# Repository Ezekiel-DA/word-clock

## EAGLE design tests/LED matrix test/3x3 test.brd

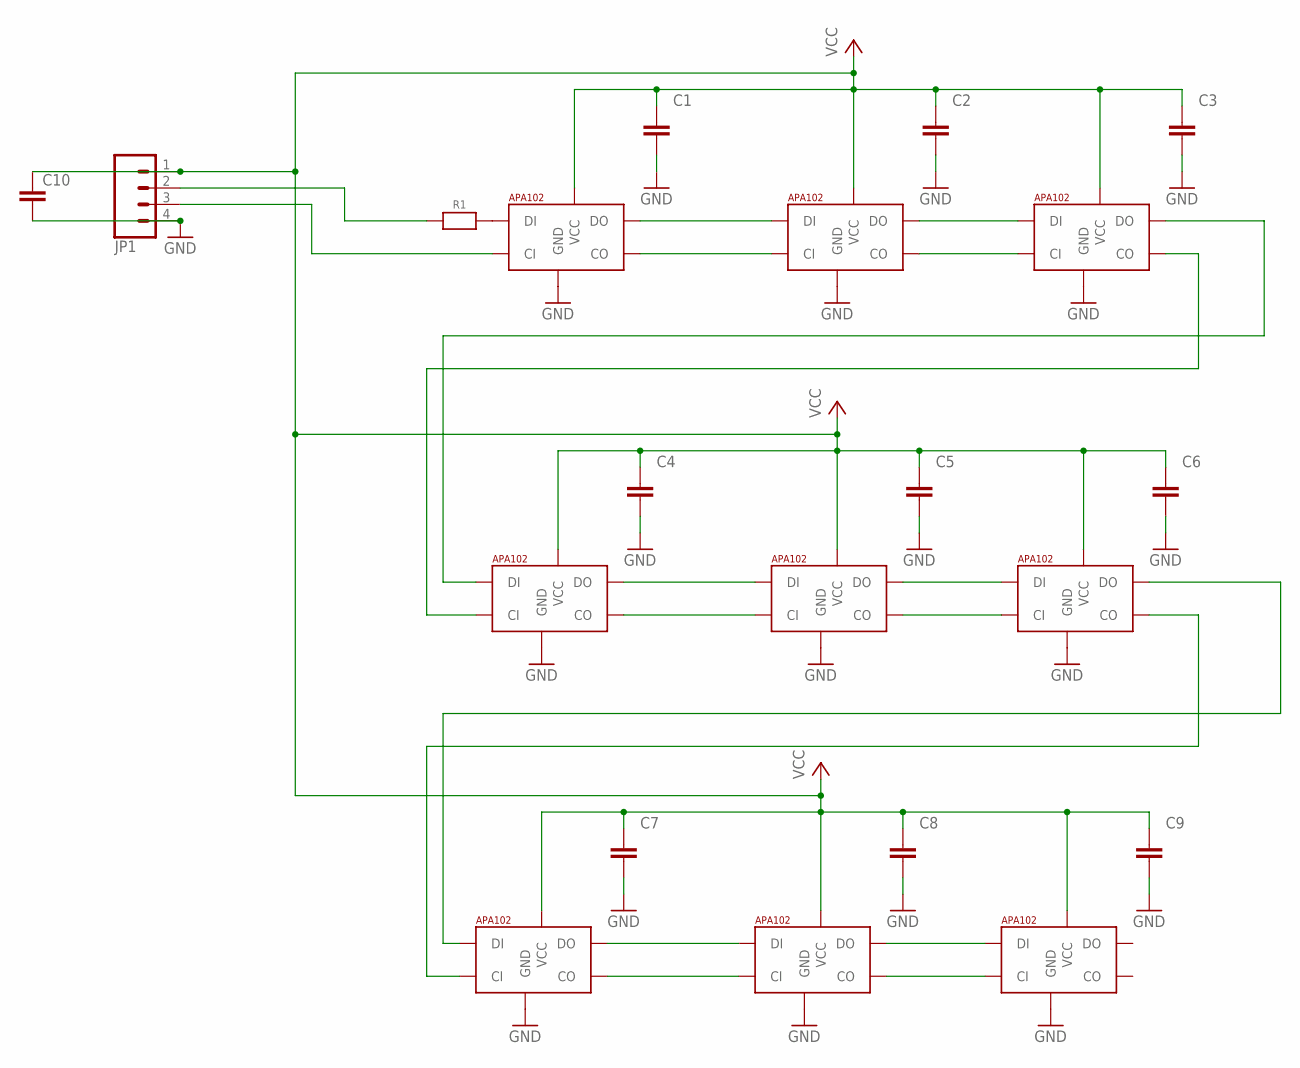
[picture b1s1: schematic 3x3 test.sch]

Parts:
C1, C2, C3, C4, C5, C6, C7, C8, C9: CAPACITOR_NPOL-0805; C805
C10: C-EUC0805; C0805
JP1: CONN_04; 1X04
R1: RESISTOR0805_NOOUTLINE; 0805-NO
U$1, U$2, U$3, U$4, U$5, U$6, U$7, U$8, U$9: APA1025050; APA102_5050

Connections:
GND: C1.2, C2.2, C3.2, C4.2, C5.2, C6.2, C7.2, C8.2, C9.2, C10.2, JP1.4, U$1.6 (GND), U$2.6 (GND), U$3.6 (GND), U$4.6 (GND), U$5.6 (GND), U$6.6 (GND), U$7.6 (GND), U$8.6 (GND), U$9.6 (GND)
unnamed: U$1.3 (DO), U$2.4 (DI)
unnamed: U$2.3 (DO), U$3.4 (DI)
unnamed: U$4.3 (DO), U$5.4 (DI)
unnamed: U$5.3 (DO), U$6.4 (DI)
unnamed: U$4.2 (CO), U$5.5 (CI)
unnamed: U$5.2 (CO), U$6.5 (CI)
unnamed: U$7.3 (DO), U$8.4 (DI)
unnamed: U$8.3 (DO), U$9.4 (DI)
unnamed: U$1.2 (CO), U$2.5 (CI)
unnamed: U$2.2 (CO), U$3.5 (CI)
unnamed: U$7.2 (CO), U$8.5 (CI)
unnamed: U$8.2 (CO), U$9.5 (CI)
unnamed: U$3.3 (DO), U$4.4 (DI)
unnamed: U$3.2 (CO), U$4.5 (CI)
unnamed: U$6.3 (DO), U$7.4 (DI)
unnamed: U$6.2 (CO), U$7.5 (CI)
unnamed: JP1.2, R1.1
unnamed: R1.2, U$1.4 (DI)
unnamed: JP1.3, U$1.5 (CI)
VCC: C1.1, C2.1, C3.1, C4.1, C5.1, C6.1, C7.1, C8.1, C9.1, C10.1, JP1.1, U$1.1 (VCC), U$2.1 (VCC), U$3.1 (VCC), U$4.1 (VCC), U$5.1 (VCC), U$6.1 (VCC), U$7.1 (VCC), U$8.1 (VCC), U$9.1 (VCC)

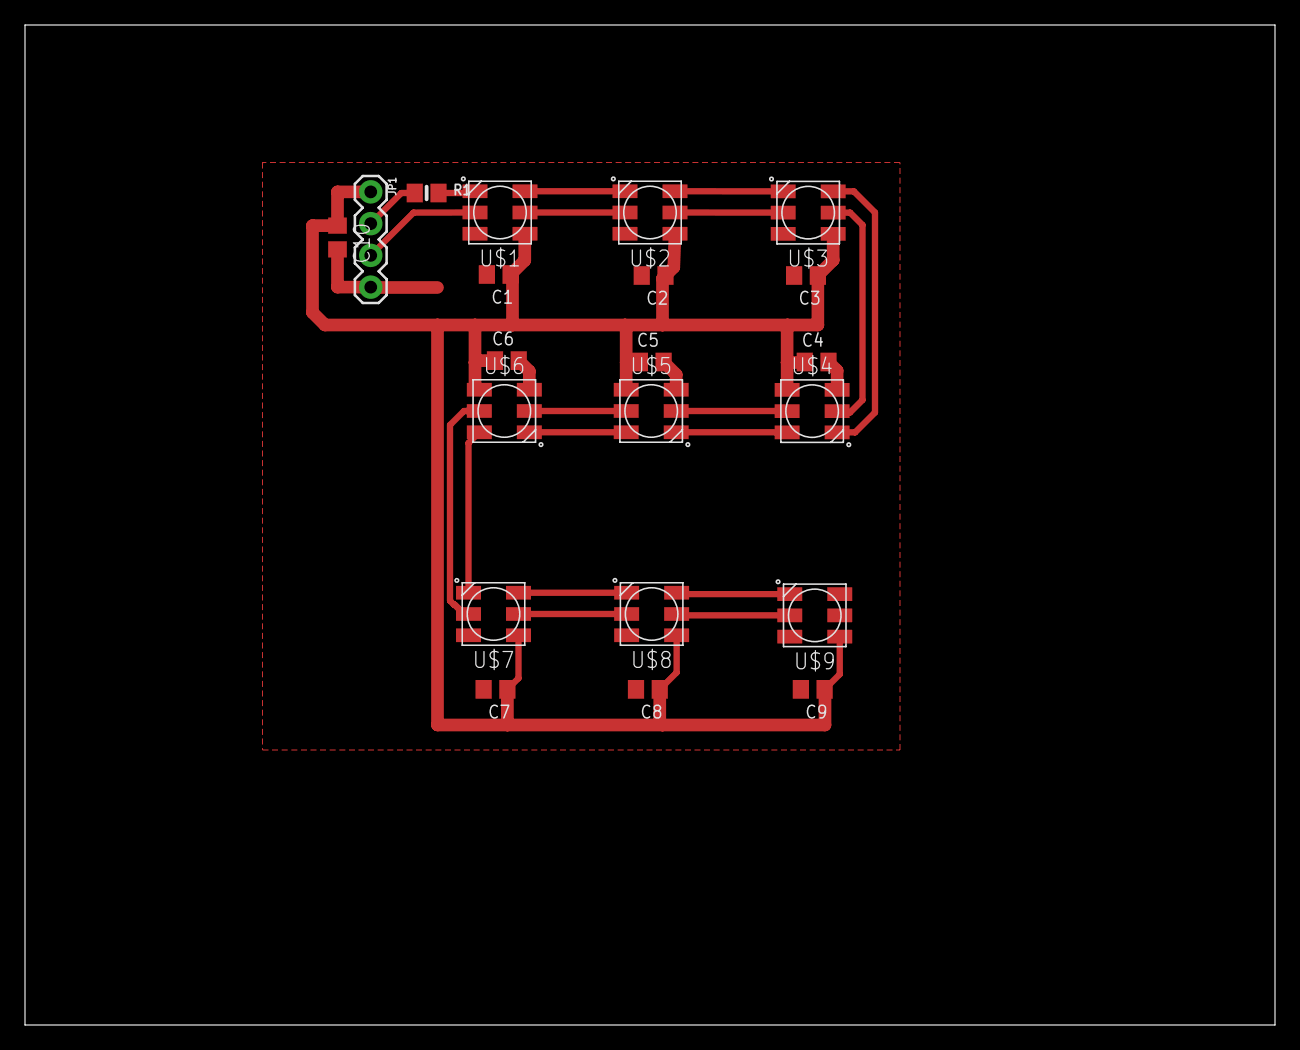
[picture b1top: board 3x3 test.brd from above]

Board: 2 copper layers, 100.0 x 80.0 mm, 21 parts (0 on the bottom side), 21 nets.

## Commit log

2017-10-03 fix LED2 position

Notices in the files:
parts and their libraries:
microbuilder: This work is placed in the public domain, and may be freely used for commercial and non-commercial work with the following conditions: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
SparkFun-Connectors: Licensing: Creative Commons ShareAlike 4.0 International - https://creativecommons.org/licenses/by-sa/4.0
